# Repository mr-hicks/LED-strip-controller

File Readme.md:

# What
A 2 channel LED strip  controller that uses as PWM signal generated by a microcontroller.

**Features**
  
  * TinyPico µC (ESP32)
  * 2 independent channels
  * Sink about 10A per channel, 5A easily
  * 12V for LED strips
  * µC or manual control
  * Manual control can be placed where-ever (6 pin ribbon connection) optional 2 USB charging ports
  * Can control multiple boards in parallel with on µC for distributed systems

# Credit
<iframe width="560" height="315" src="https://www.youtube.com/embed/DhbMnQt14_o" frameborder="0" allow="accelerometer; autoplay; encrypted-media; gyroscope; picture-in-picture" allowfullscreen></iframe>

But, I wanted it to be self setting time wise so that it could automatically come on in the morning or off in the evening.

# Sections
## Power
Two input options, dc barrel or bare wire.
Barrel is intended for lower power smaller applications (I'm intending lamps), bare wire for higher power.  Example, light fixture.

Then a fuse and a 1k and 14V zener in parallel.
The resistor is a bleeder for capacitors.
The zener is to protect the caps from overvoltage.

## PWM

## 

# Other stuff

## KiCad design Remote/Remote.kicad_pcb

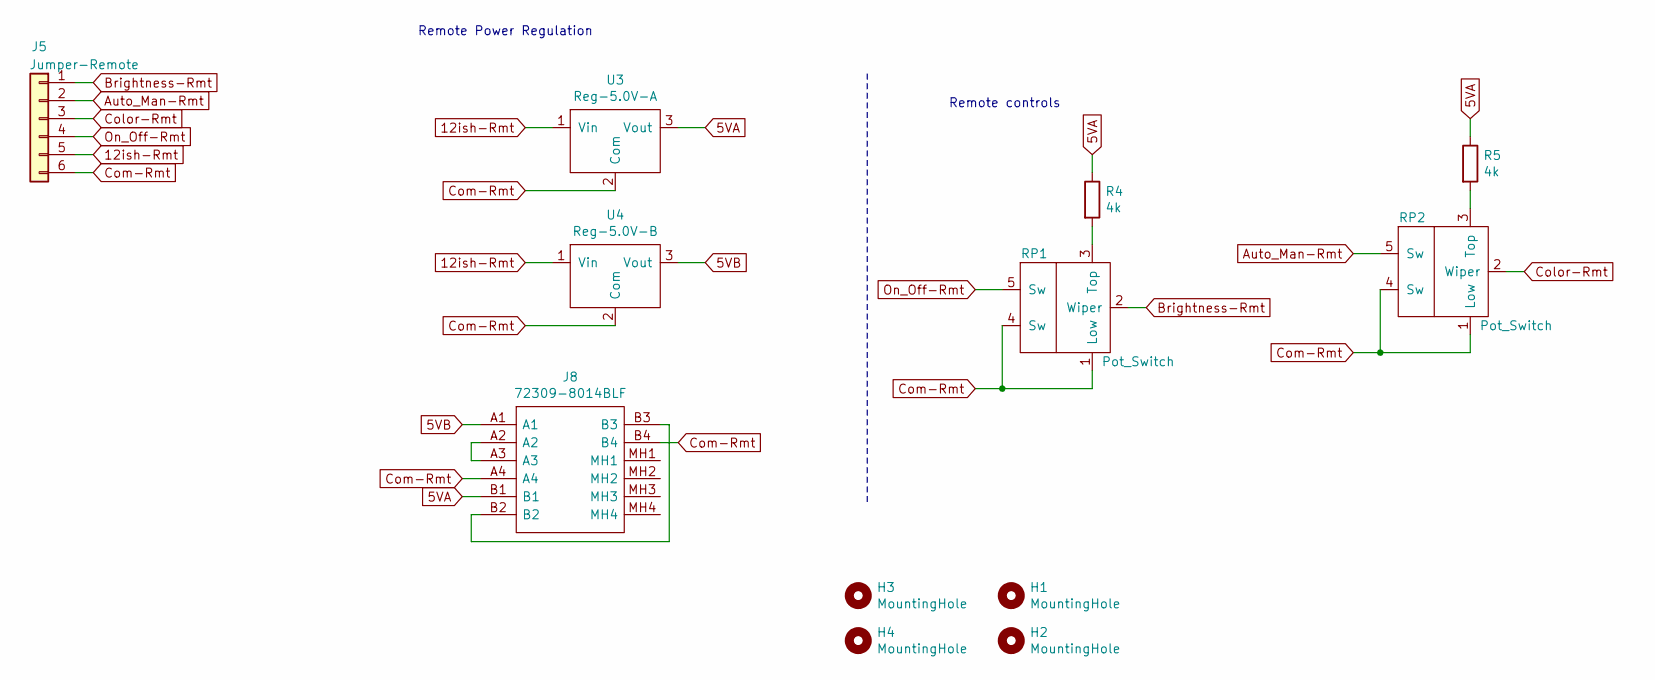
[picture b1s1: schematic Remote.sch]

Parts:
H1, H2, H3, H4: MountingHole; MountingHole_2.2mm_M2_Pad
J5: Jumper-Remote; 21787106
J8: 72309-8014BLF; 723098014BLF; Mouser Part Number 649-72309-8014BLF
R4, R5: 4k; R_Axial_DIN0204_L3.6mm_D1.6mm_P5.08mm_Horizontal
RP1, RP2: Pot_Switch; pot_switch
U3: Reg-5.0V-A; 5.0V-Reg
U4: Reg-5.0V-B; 5.0V-Reg

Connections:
5VA: J8.B1, R4.1, R5.1, U3.3 (Vout)
5VB: J8.A1, U4.3 (Vout)
12ish-Rmt: J5.5, U3.1 (Vin), U4.1 (Vin)
Auto_Man-Rmt: J5.2, RP2.5 (Sw)
Brightness-Rmt: J5.1, RP1.2 (Wiper)
Color-Rmt: J5.3, RP2.2 (Wiper)
Com-Rmt: J5.6, J8.A4, J8.B4, RP1.1 (Low), RP1.4 (Sw), RP2.1 (Low), RP2.4 (Sw), U3.2 (Com), U4.2 (Com)
unnamed: J8.A2, J8.A3
unnamed: J8.B2, J8.B3
unnamed: R4.2, RP1.3 (Top)
unnamed: R5.2, RP2.3 (Top)
On_Off-Rmt: J5.4, RP1.5 (Sw)

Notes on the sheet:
Remote Power Regulation
Remote controls

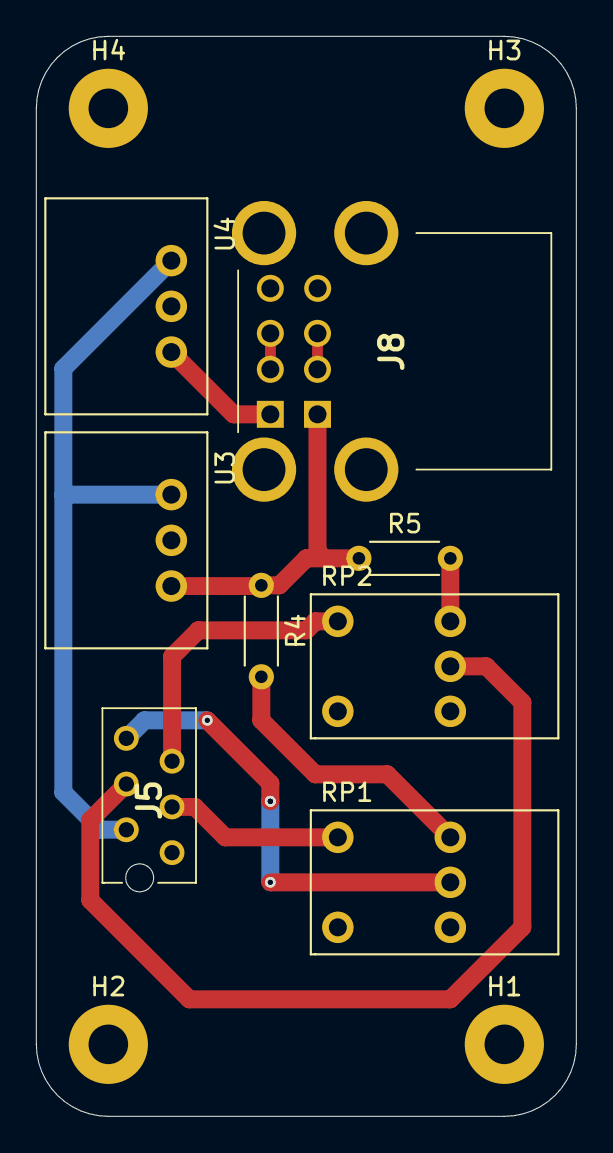
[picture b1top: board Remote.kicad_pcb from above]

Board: 2 copper layers, 30.0 x 60.0 mm, 12 parts (0 on the bottom side), 12 nets.

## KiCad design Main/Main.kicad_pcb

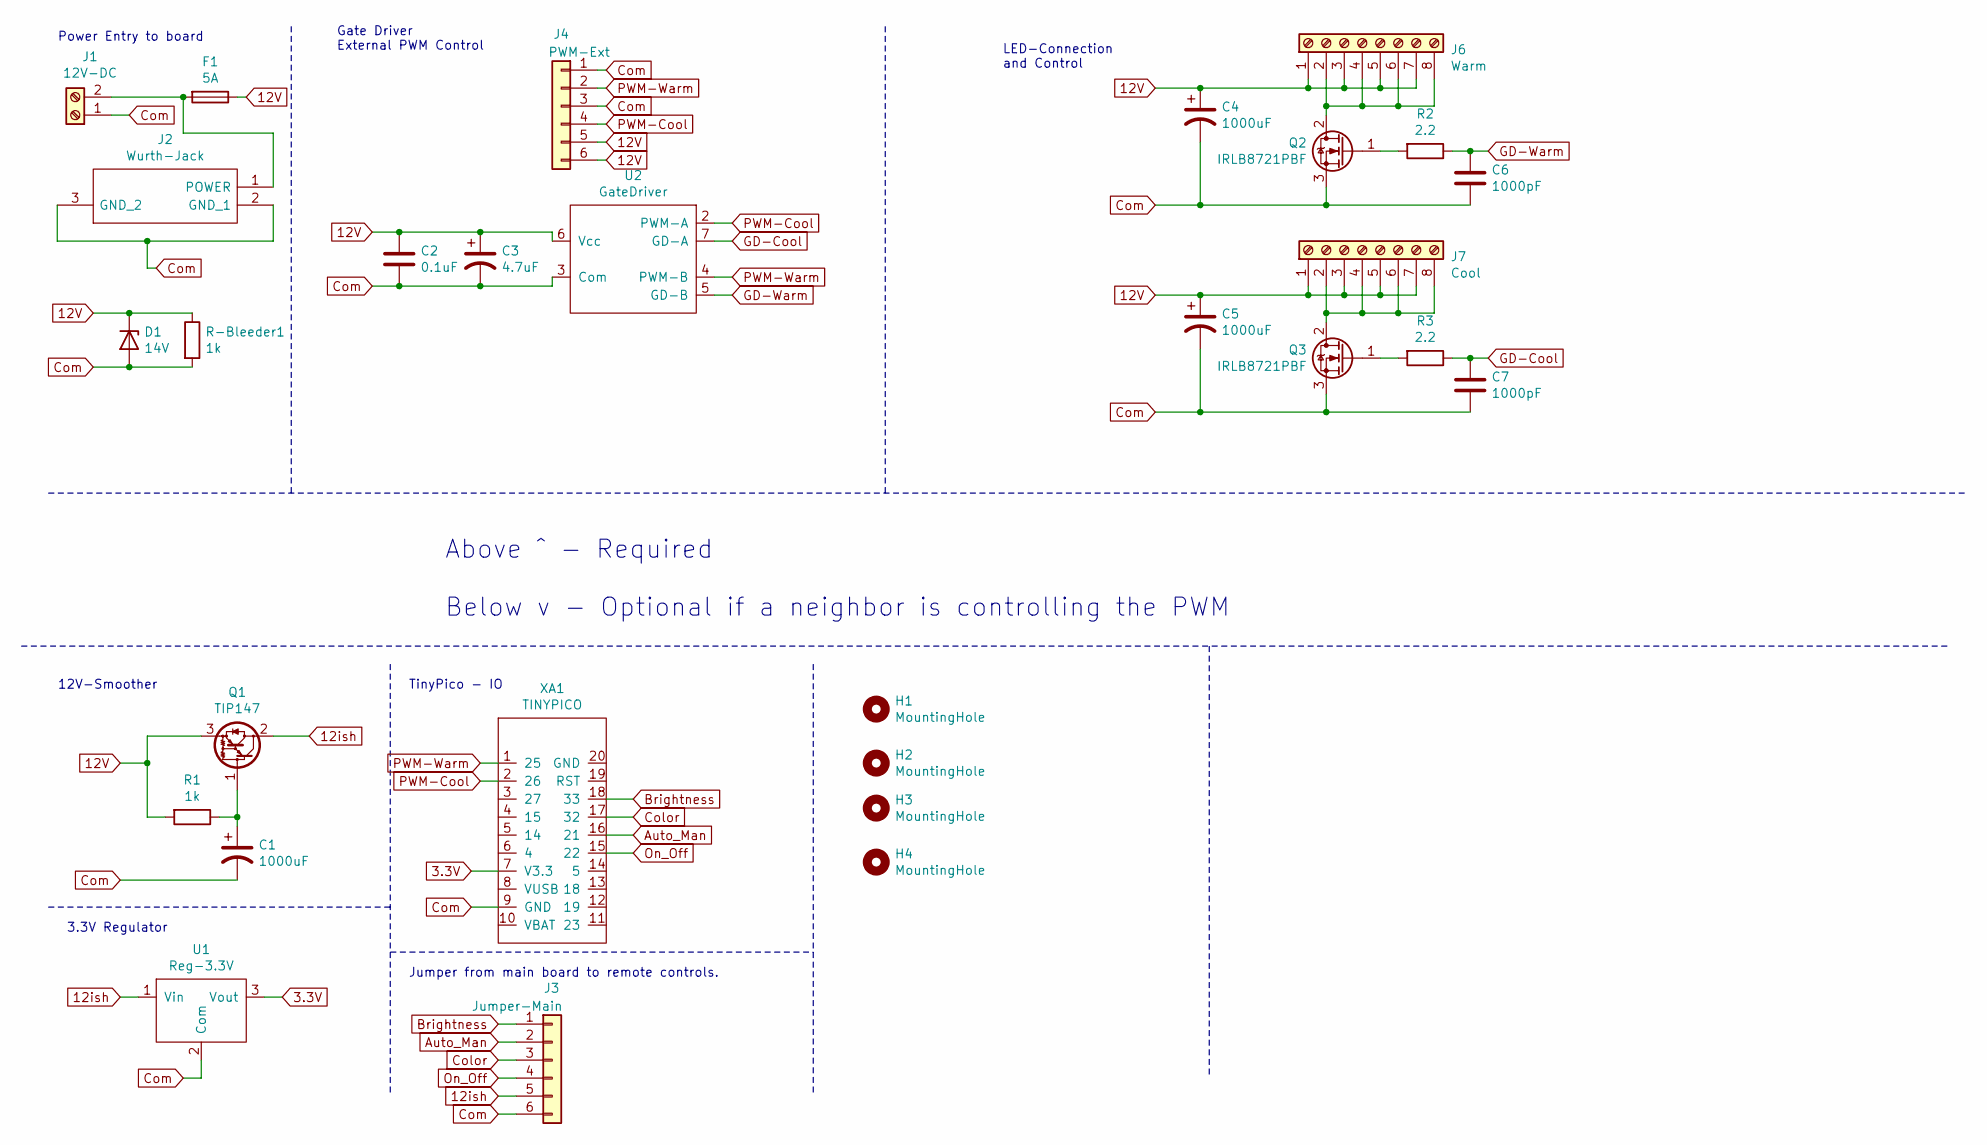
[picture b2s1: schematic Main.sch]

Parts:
C1, C4, C5: 1000uF; CP_Radial_D10.0mm_P5.00mm
C2: 0.1uF; C_Rect_L7.2mm_W2.5mm_P5.00mm_FKS2_FKP2_MKS2_MKP2
C3: 4.7uF; CP_Radial_D5.0mm_P2.00mm
C6, C7: 1000pF; C_Rect_L7.2mm_W2.5mm_P5.00mm_FKS2_FKP2_MKS2_MKP2
D1: 14V; D_DO-35_SOD27_P7.62mm_Horizontal
F1: 5A; 4527
H1, H2, H3, H4: MountingHole; MountingHole_2.2mm_M2_Pad
J1: 12V-DC; CUI_TBL005A-500-02GY-2WT
J2: Wurth-Jack; 694106301002_1; Mouser Part Number 710-694106301002
J3: Jumper-Main; 21787106
J4: PWM-Ext; 21787106
J6: Warm; CUI_TBL005A-500-08GY-2WT
J7: Cool; CUI_TBL005A-500-08GY-2WT
Q1: TIP147; TO-220-3_Vertical
Q2, Q3: IRLB8721PBF; TO-220-3_Vertical
R1: 1k; R_Axial_DIN0204_L3.6mm_D1.6mm_P5.08mm_Horizontal
R2, R3: 2.2; R_Axial_DIN0207_L6.3mm_D2.5mm_P7.62mm_Horizontal
R-Bleeder1: 1k; R_Axial_DIN0204_L3.6mm_D1.6mm_P5.08mm_Horizontal
U1: Reg-3.3V; 3.3V-Reg
U2: GateDriver; DIP-8_W7.62mm_Socket
XA1: TINYPICO; _usr_TINYPICO

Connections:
3.3V: U1.3 (Vout), XA1.7 (V3.3)
12V: C2.1, C3.1, C4.1, C5.1, D1.1 (K), F1.1, J4.5, J4.6, J6.1, J6.3, J6.5, J6.7, J7.1, J7.3, J7.5, J7.7, Q1.3 (E), R1.2, R-Bleeder1.1, U2.6 (Vcc)
12ish: J3.5, Q1.2 (C), U1.1 (Vin)
Auto_Man: J3.2, XA1.16 (21)
Brightness: J3.1, XA1.18 (33)
Color: J3.3, XA1.17 (32)
Com: C1.2, C2.2, C3.2, C4.2, C5.2, C6.2, C7.2, D1.2 (A), J1.1, J2.2 (GND_1), J2.3 (GND_2), J3.6, J4.1, J4.3, Q2.3 (S), Q3.3 (S), R-Bleeder1.2, U1.2 (Com), U2.3 (Com), XA1.9 (GND)
GD-Cool: C7.1, R3.1, U2.7 (GD-A)
GD-Warm: C6.1, R2.1, U2.5 (GD-B)
unnamed: C1.1, Q1.1 (B), R1.1
unnamed: F1.2, J1.2, J2.1 (POWER)
unnamed: J6.2, J6.4, J6.6, J6.8, Q2.2 (D)
unnamed: J7.2, J7.4, J7.6, J7.8, Q3.2 (D)
unnamed: Q2.1 (G), R2.2
unnamed: Q3.1 (G), R3.2
On_Off: J3.4, XA1.15 (22)
PWM-Cool: J4.4, U2.2 (PWM-A), XA1.2 (26)
PWM-Warm: J4.2, U2.4 (PWM-B), XA1.1 (25)

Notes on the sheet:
Power Entry to board
Gate Driver External PWM Control
LED-Connection and Control
12V-Smoother
3.3V Regulator
Jumper from main board to remote controls.
TinyPico - IO
Above ^ - Required Below v - Optional if a neighbor is controlling the PWM

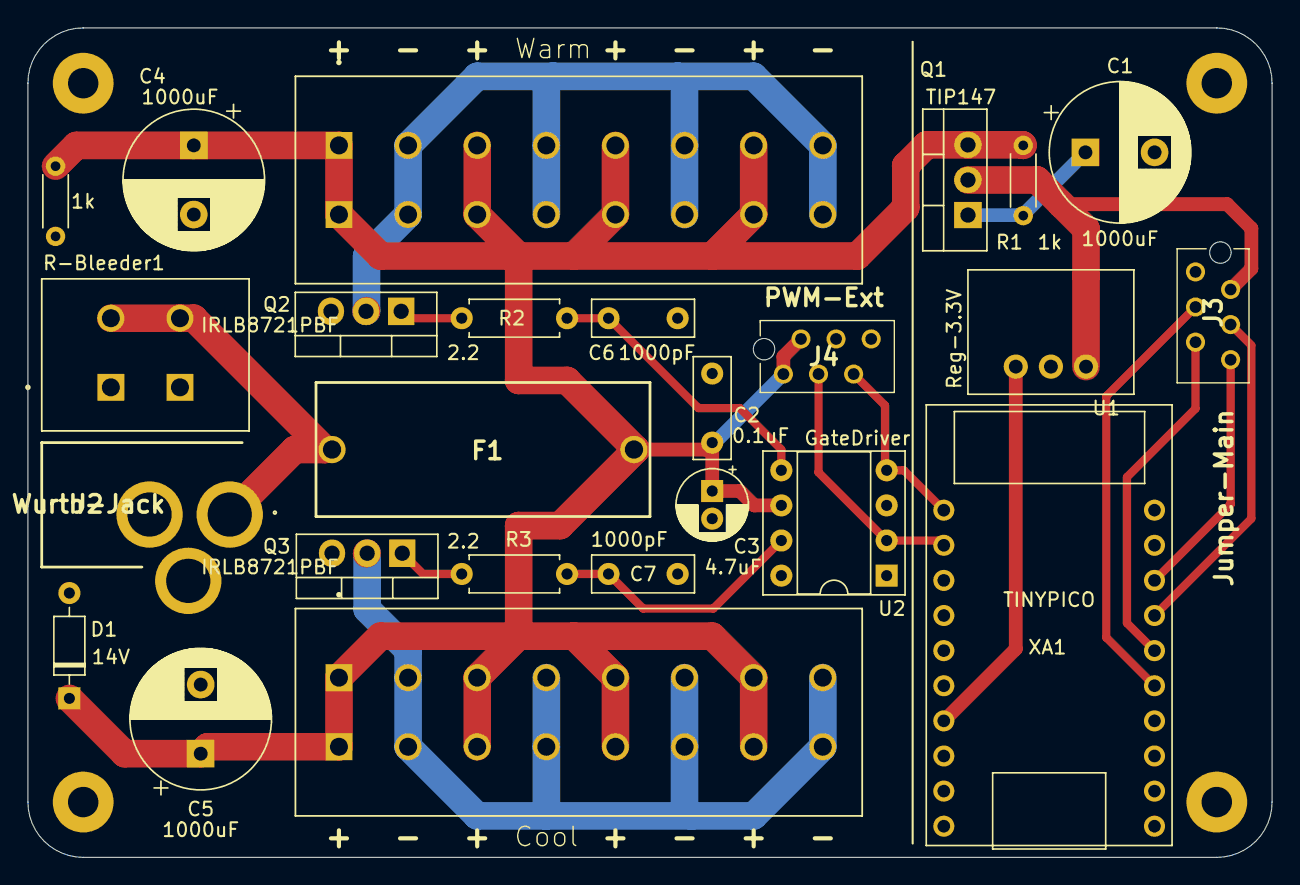
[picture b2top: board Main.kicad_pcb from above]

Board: 2 copper layers, 90.0 x 60.0 mm, 29 parts (0 on the bottom side), 18 nets.

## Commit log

2020-08-19 Upload work
2020-08-28 testing ADC, GPIO
